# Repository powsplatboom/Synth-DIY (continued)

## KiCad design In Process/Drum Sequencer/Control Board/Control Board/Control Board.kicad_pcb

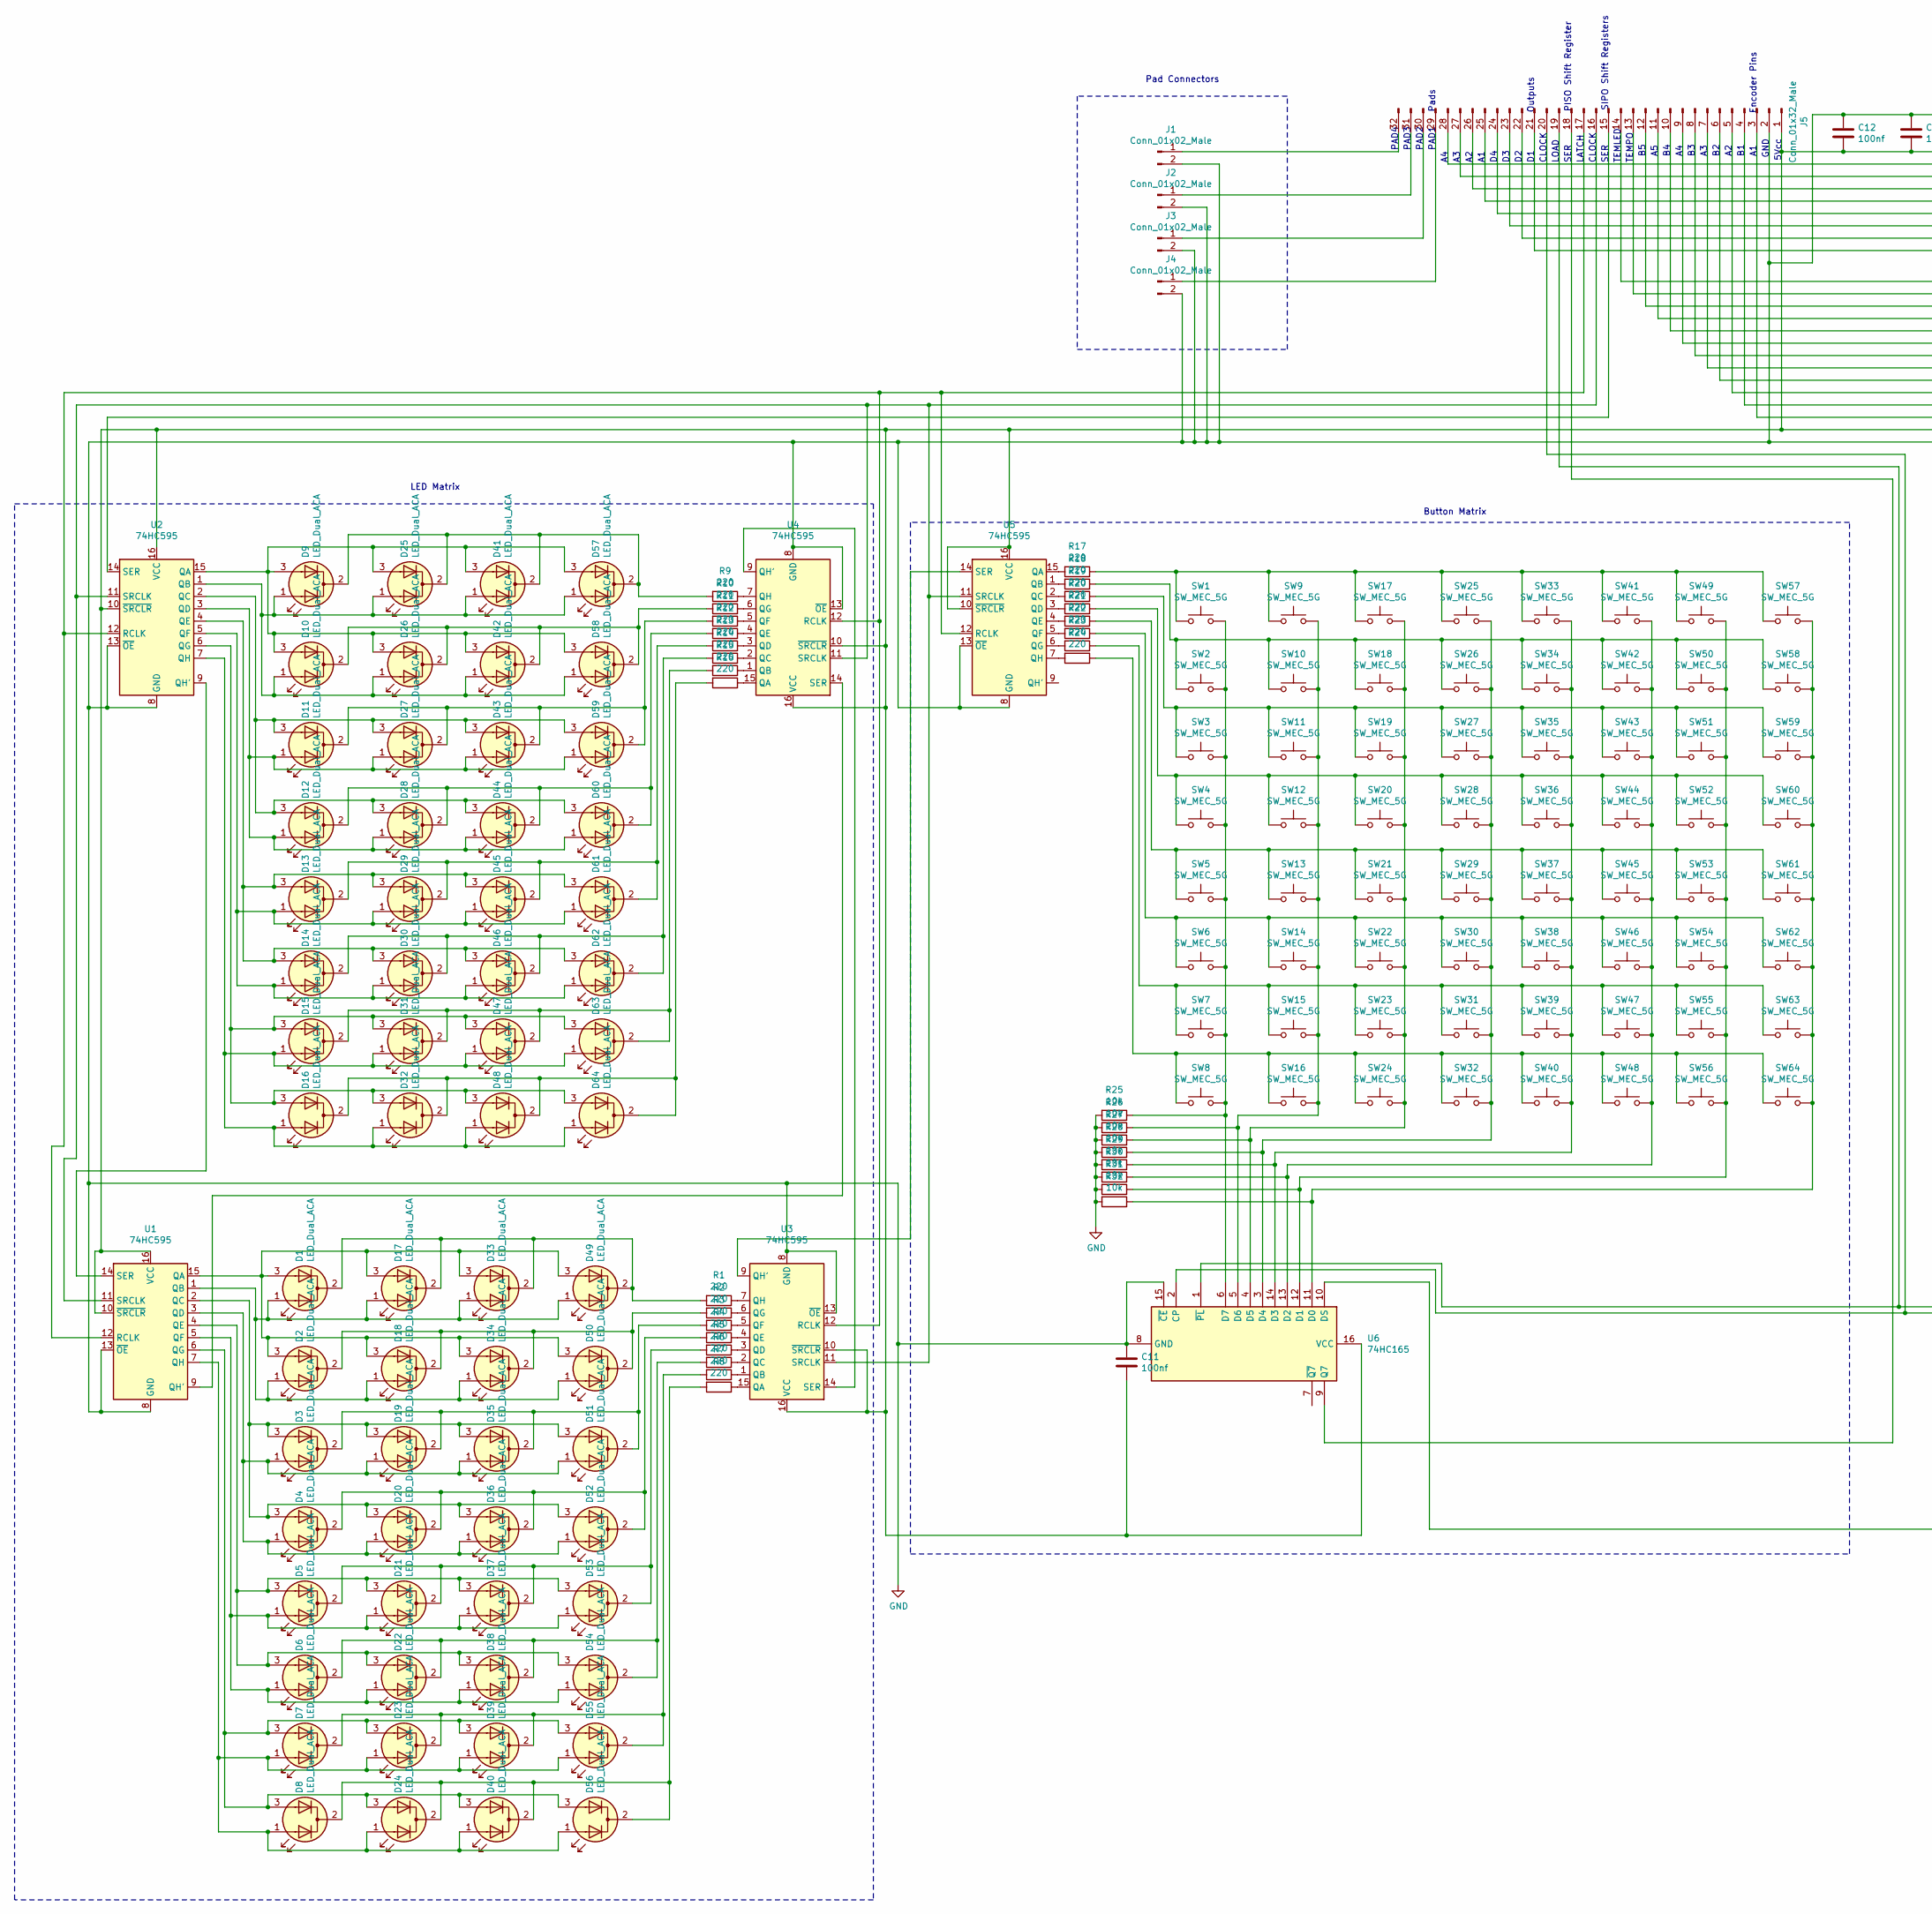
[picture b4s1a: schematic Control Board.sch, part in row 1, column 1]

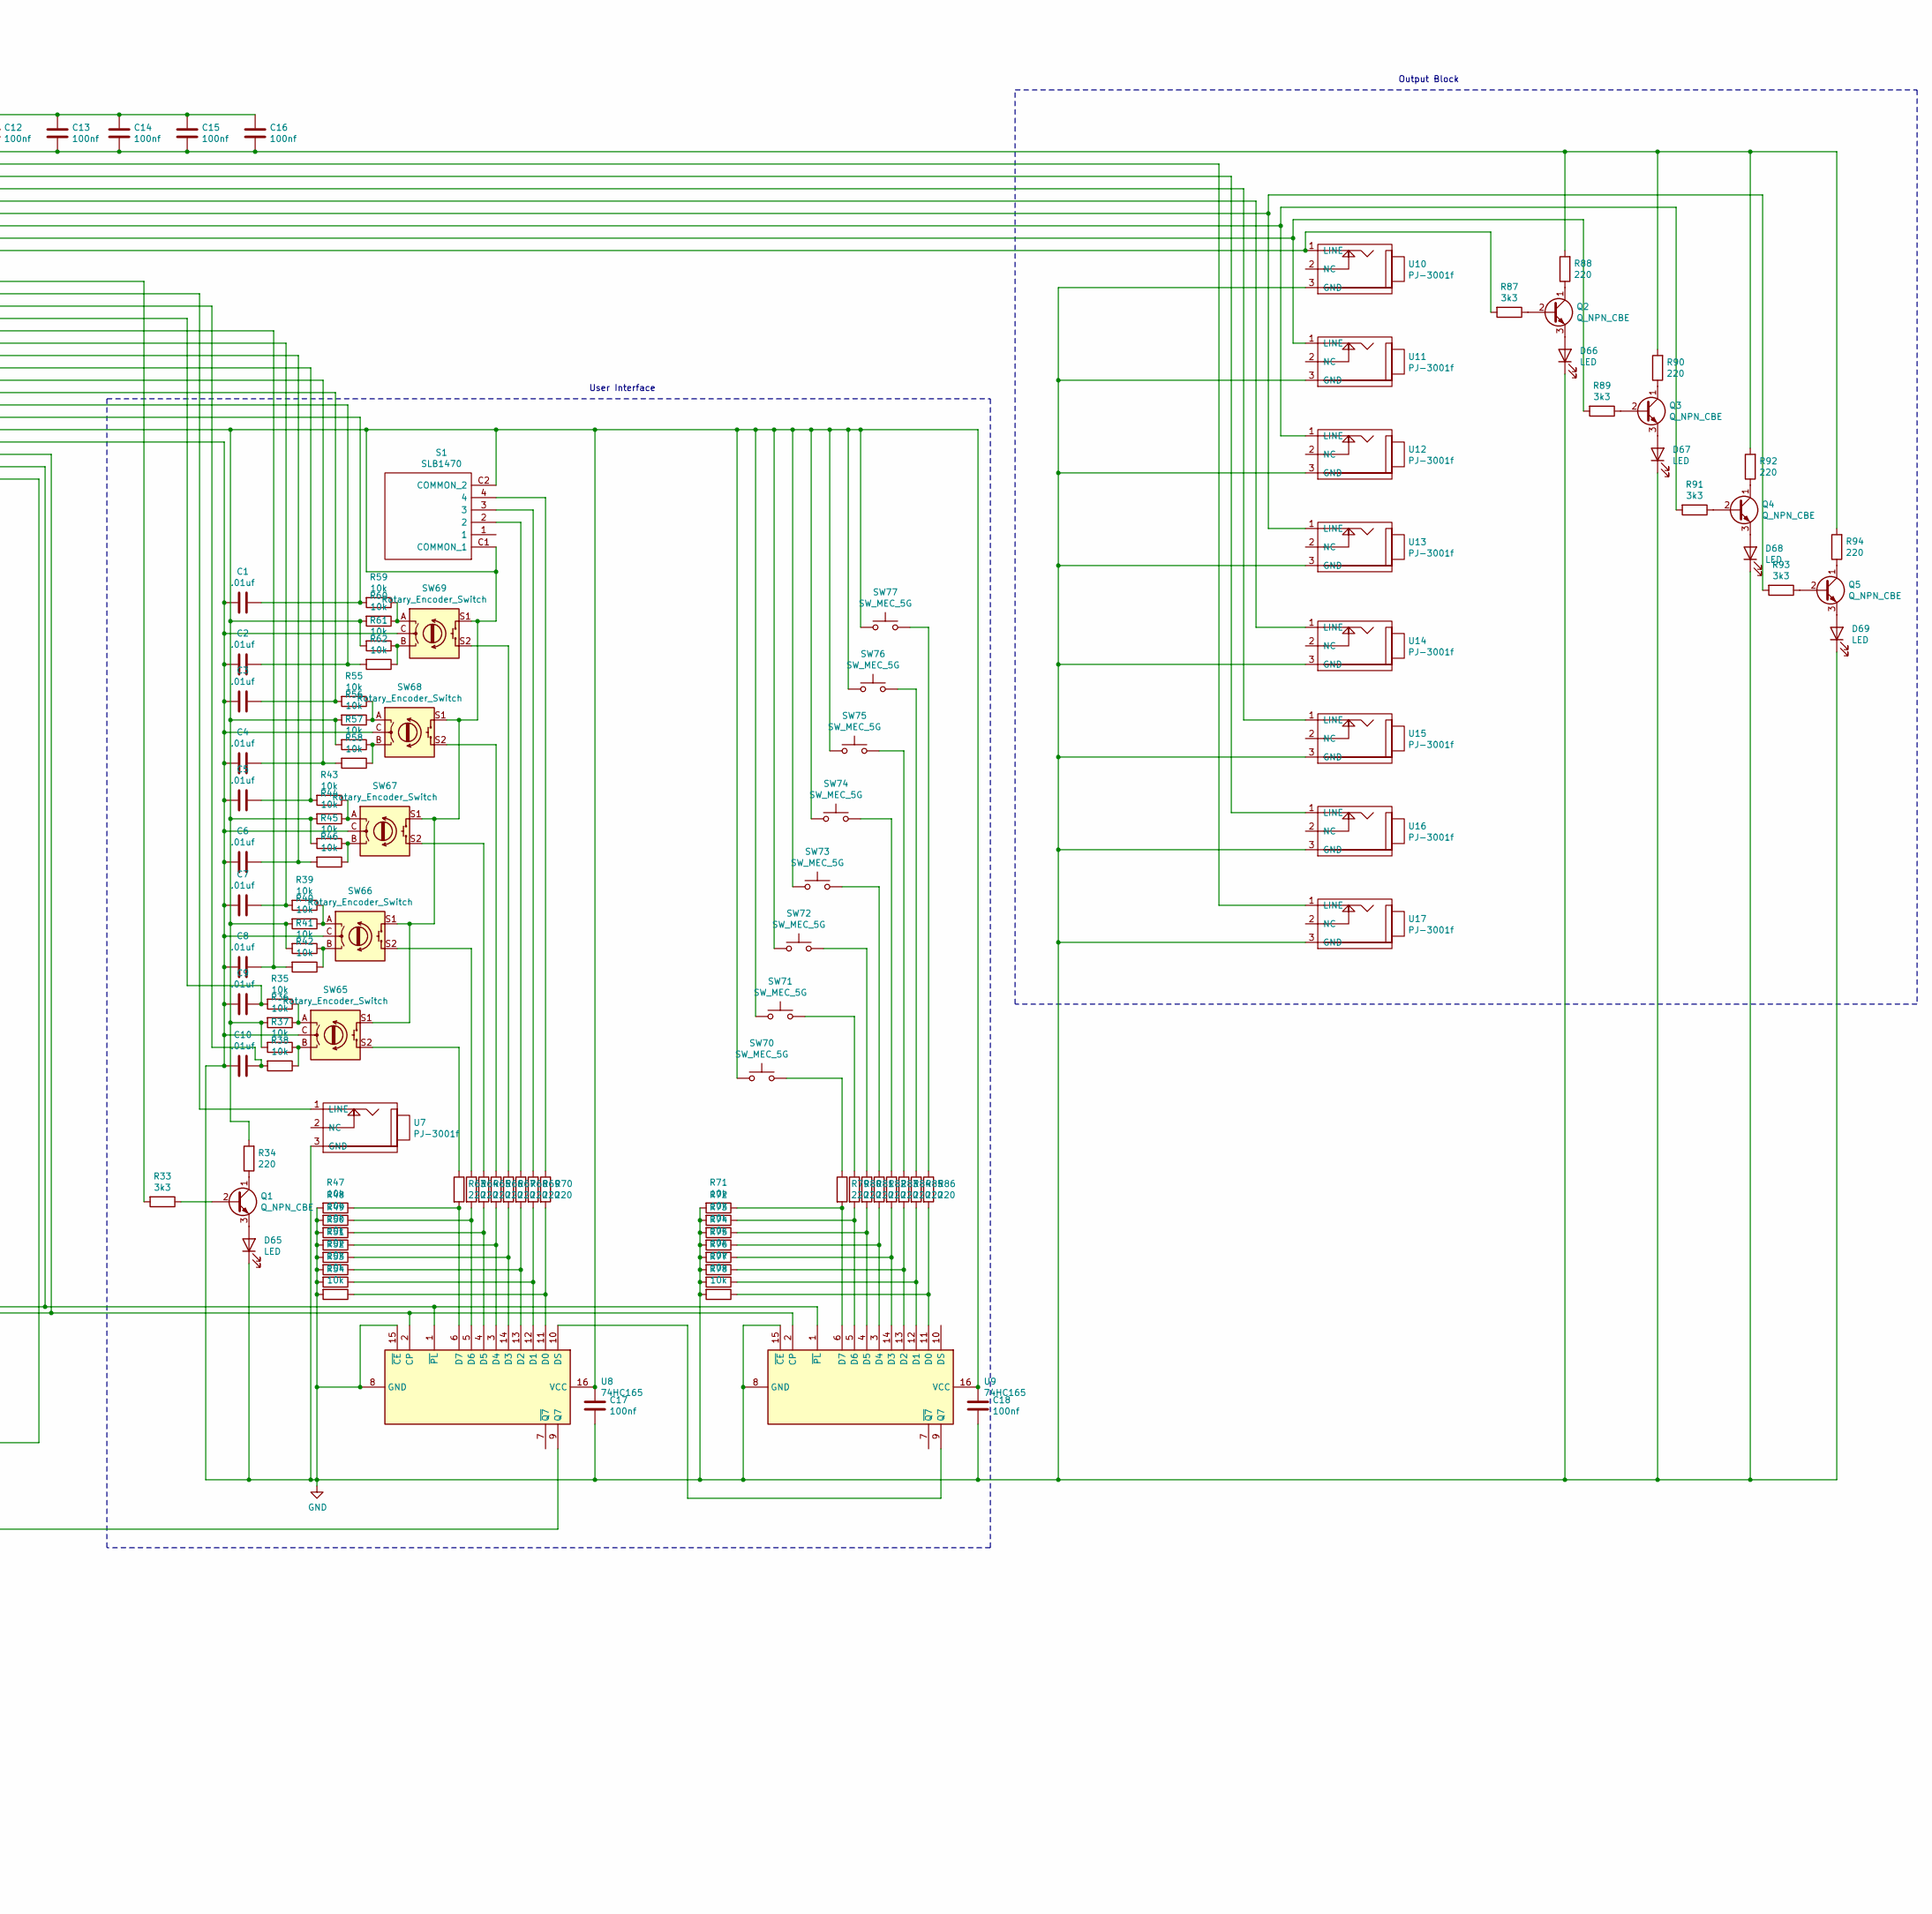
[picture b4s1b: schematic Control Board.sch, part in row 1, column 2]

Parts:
C1, C2, C3, C4, C5, C6, C7, C8, C9, C10: .01uf; C_0805_2012Metric
C11, C12, C13, C14, C15, C16, C17, C18: 100nf; C_0805_2012Metric
D1, D2, D3, D4, D5, D6, D7, D8, D9, D10, D11, D12, D13, D14, D15, D16, D17, D18, D19, D20, D21, D22, D23, D24, D25, D26, D27, D28, D29, D30, D31, D32, D33, D34, D35, D36, D37, D38, D39, D40, D41, D42, D43, D44, D45, D46, D47, D48, D49, D50, D51, D52, D53, D54, D55, D56, D57, D58, D59, D60, D61, D62, D63, D64: LED_Dual_ACA; LED_D3.0mm-3
D65, D66, D67, D68, D69: LED; LED_D5.0mm
J1, J2, J3, J4: Conn_01x02_Male; JST_XH_B2B-XH-AM_1x02_P2.50mm_Vertical
J5: Conn_01x32_Male; PinHeader_1x32_P2.54mm_Vertical
Q1, Q2, Q3, Q4, Q5: Q_NPN_CBE; TO-92_Inline
R1, R2, R3, R4, R5, R6, R7, R8, R9, R10, R11, R12, R13, R14, R15, R16, R17, R18, R19, R20, R21, R22, R23, R24, R34, R63, R64, R65, R66, R67, R68, R69, R70, R79, R80, R81, R82, R83, R84, R85, R86, R88, R90, R92, R94: 220; R_1206_3216Metric_Pad1.30x1.75mm_HandSolder
R25, R26, R27, R28, R29, R30, R31, R32, R35, R36, R37, R38, R39, R40, R41, R42, R43, R44, R45, R46, R47, R48, R49, R50, R51, R52, R53, R54, R55, R56, R57, R58, R59, R60, R61, R62, R71, R72, R73, R74, R75, R76, R77, R78: 10k; R_1206_3216Metric_Pad1.30x1.75mm_HandSolder
R33, R87, R89, R91, R93: 3k3; R_0805_2012Metric_Pad1.20x1.40mm_HandSolder
S1: SLB1470; Manufacturer_Part_Number SLB1470; Mouser Part Number 642-SLB1470
SW1, SW2, SW3, SW4, SW5, SW6, SW7, SW8, SW9, SW10, SW11, SW12, SW13, SW14, SW15, SW16, SW17, SW18, SW19, SW20, SW21, SW22, SW23, SW24, SW25, SW26, SW27, SW28, SW29, SW30, SW31, SW32, SW33, SW34, SW35, SW36, SW37, SW38, SW39, SW40, SW41, SW42, SW43, SW44, SW45, SW46, SW47, SW48, SW49, SW50, SW51, SW52, SW53, SW54, SW55, SW56, SW57, SW58, SW59, SW60, SW61, SW62, SW63, SW64, SW70, SW71, SW72, SW73, SW74, SW75, SW76, SW77: SW_MEC_5G; SW_PUSH_6mm
SW65, SW66, SW67, SW68, SW69: Rotary_Encoder_Switch; RotaryEncoder_Alps_EC11E-Switch_Vertical_H20mm
U1, U2, U3, U4, U5: 74HC595; SO-16_3.9x9.9mm_P1.27mm
U6, U8: 74HC165; SO-16_3.9x9.9mm_P1.27mm
U7, U10, U11, U12, U13, U14, U15, U16, U17: PJ-3001f; PJ-3001_Mono_Phone
U9: 74HC165; SOIC-16_3.9x9.9mm_P1.27mm

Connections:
GND: C1.2, C2.2, C3.2, C4.2, C5.2, C6.2, C7.2, C8.2, C9.2, C10.2, C11.1, C12.1, C13.1, C14.1, C15.1, C16.1, C17.2, C18.2, D65.1 (K), D66.1 (K), D67.1 (K), D68.1 (K), D69.1 (K), J1.2, J2.2, J3.2, J4.2, J5.2, R25.2, R26.2, R27.2, R28.2, R29.2, R30.2, R31.2, R32.2, R47.2, R48.2, R49.2, R50.2, R51.2, R52.2, R53.2, R54.2, R71.2, R72.2, R73.2, R74.2, R75.2, R76.2, R77.2, R78.2, SW65.C, SW66.C, SW67.C, SW68.C, SW69.C, U1.8 (GND), U1.13 (~OE), U2.8 (GND), U2.13 (~OE), U3.8 (GND), U3.13 (~OE), U4.8 (GND), U4.13 (~OE), U5.8 (GND), U5.13 (~OE), U6.8 (GND), U6.15 (~CE), U7.3 (GND), U8.8 (GND), U8.15 (~CE), U9.8 (GND), U9.15 (~CE), U10.3 (GND), U11.3 (GND), U12.3 (GND), U13.3 (GND), U14.3 (GND), U15.3 (GND), U16.3 (GND), U17.3 (GND)
unnamed: C1.1, J5.3, R59.2
unnamed: C2.1, J5.4, R62.2
unnamed: C3.1, J5.5, R55.2
unnamed: C4.1, J5.6, R58.2
unnamed: C5.1, J5.7, R43.2
unnamed: C6.1, J5.8, R46.2
unnamed: C7.1, J5.9, R39.2
unnamed: C8.1, J5.10, R42.2
unnamed: C9.1, J5.11, R35.2
unnamed: C10.1, J5.12, R38.2
unnamed: C11.2, C12.2, C13.2, C14.2, C15.2, C16.2, C17.1, C18.1, J5.1, R34.2, R36.2, R37.2, R40.2, R41.2, R44.2, R45.2, R56.2, R57.2, R60.2, R61.2, R88.2, R90.2, R92.2, R94.2, S1.C1 (COMMON_1), S1.C2 (COMMON_2), SW65.S1, SW66.S1, SW67.S1, SW68.S1, SW69.S1, SW70.1 (A), SW71.1 (A), SW72.1 (A), SW73.1 (A), SW74.1 (A), SW75.1 (A), SW76.1 (A), SW77.1 (A), U1.10 (~SRCLR), U1.16 (VCC), U2.10 (~SRCLR), U2.16 (VCC), U3.10 (~SRCLR), U3.16 (VCC), U4.10 (~SRCLR), U4.16 (VCC), U5.10 (~SRCLR), U5.16 (VCC), U6.16 (VCC), U8.16 (VCC), U9.16 (VCC)
unnamed: D1.1 (A1), D2.1 (A1), D17.1 (A1), D18.1 (A1), D33.1 (A1), D34.1 (A1), D49.1 (A1), D50.1 (A1), U1.1 (QB)
unnamed: D1.2 (K), D17.2 (K), D33.2 (K), D49.2 (K), R1.2
unnamed: D1.3 (A2), D2.3 (A2), D17.3 (A2), D18.3 (A2), D33.3 (A2), D34.3 (A2), D49.3 (A2), D50.3 (A2), U1.15 (QA)
unnamed: D9.1 (A1), D10.1 (A1), D25.1 (A1), D26.1 (A1), D41.1 (A1), D42.1 (A1), D57.1 (A1), D58.1 (A1), U2.1 (QB)
unnamed: D10.2 (K), D26.2 (K), D42.2 (K), D58.2 (K), R10.2
unnamed: D9.3 (A2), D10.3 (A2), D25.3 (A2), D26.3 (A2), D41.3 (A2), D42.3 (A2), D57.3 (A2), D58.3 (A2), U2.15 (QA)
unnamed: D11.1 (A1), D12.1 (A1), D27.1 (A1), D28.1 (A1), D43.1 (A1), D44.1 (A1), D59.1 (A1), D60.1 (A1), U2.3 (QD)
unnamed: D11.2 (K), D27.2 (K), D43.2 (K), D59.2 (K), R11.2
unnamed: D11.3 (A2), D12.3 (A2), D27.3 (A2), D28.3 (A2), D43.3 (A2), D44.3 (A2), D59.3 (A2), D60.3 (A2), U2.2 (QC)
unnamed: D12.2 (K), D28.2 (K), D44.2 (K), D60.2 (K), R12.2
unnamed: D13.1 (A1), D14.1 (A1), D29.1 (A1), D30.1 (A1), D45.1 (A1), D46.1 (A1), D61.1 (A1), D62.1 (A1), U2.5 (QF)
unnamed: D13.2 (K), D29.2 (K), D45.2 (K), D61.2 (K), R13.2
unnamed: D13.3 (A2), D14.3 (A2), D29.3 (A2), D30.3 (A2), D45.3 (A2), D46.3 (A2), D61.3 (A2), D62.3 (A2), U2.4 (QE)
unnamed: D14.2 (K), D30.2 (K), D46.2 (K), D62.2 (K), R14.2
unnamed: D15.1 (A1), D16.1 (A1), D31.1 (A1), D32.1 (A1), D47.1 (A1), D48.1 (A1), D63.1 (A1), D64.1 (A1), U2.7 (QH)
unnamed: D15.2 (K), D31.2 (K), D47.2 (K), D63.2 (K), R15.2
unnamed: D15.3 (A2), D16.3 (A2), D31.3 (A2), D32.3 (A2), D47.3 (A2), D48.3 (A2), D63.3 (A2), D64.3 (A2), U2.6 (QG)
unnamed: D16.2 (K), D32.2 (K), D48.2 (K), D64.2 (K), R16.2
unnamed: D2.2 (K), D18.2 (K), D34.2 (K), D50.2 (K), R2.2
unnamed: D3.1 (A1), D4.1 (A1), D19.1 (A1), D20.1 (A1), D35.1 (A1), D36.1 (A1), D51.1 (A1), D52.1 (A1), U1.3 (QD)
unnamed: D3.2 (K), D19.2 (K), D35.2 (K), D51.2 (K), R3.2
unnamed: D3.3 (A2), D4.3 (A2), D19.3 (A2), D20.3 (A2), D35.3 (A2), D36.3 (A2), D51.3 (A2), D52.3 (A2), U1.2 (QC)
unnamed: D4.2 (K), D20.2 (K), D36.2 (K), D52.2 (K), R4.2
unnamed: D5.1 (A1), D6.1 (A1), D21.1 (A1), D22.1 (A1), D37.1 (A1), D38.1 (A1), D53.1 (A1), D54.1 (A1), U1.5 (QF)
unnamed: D5.2 (K), D21.2 (K), D37.2 (K), D53.2 (K), R5.2
unnamed: D5.3 (A2), D6.3 (A2), D21.3 (A2), D22.3 (A2), D37.3 (A2), D38.3 (A2), D53.3 (A2), D54.3 (A2), U1.4 (QE)
unnamed: D6.2 (K), D22.2 (K), D38.2 (K), D54.2 (K), R6.2
unnamed: D7.1 (A1), D8.1 (A1), D23.1 (A1), D24.1 (A1), D39.1 (A1), D40.1 (A1), D55.1 (A1), D56.1 (A1), U1.7 (QH)
unnamed: D7.2 (K), D23.2 (K), D39.2 (K), D55.2 (K), R7.2
unnamed: D7.3 (A2), D8.3 (A2), D23.3 (A2), D24.3 (A2), D39.3 (A2), D40.3 (A2), D55.3 (A2), D56.3 (A2), U1.6 (QG)
unnamed: D8.2 (K), D24.2 (K), D40.2 (K), D56.2 (K), R8.2
unnamed: D9.2 (K), D25.2 (K), D41.2 (K), D57.2 (K), R9.2
unnamed: D65.2 (A), Q1.3 (E)
unnamed: D66.2 (A), Q2.3 (E)
unnamed: D67.2 (A), Q3.3 (E)
unnamed: D68.2 (A), Q4.3 (E)
unnamed: D69.2 (A), Q5.3 (E)
unnamed: J1.1, J5.32
unnamed: J2.1, J5.31
unnamed: J3.1, J5.30
unnamed: J4.1, J5.29
unnamed: J5.13, U7.1 (LINE)
unnamed: J5.14, R33.2
unnamed: J5.15, U2.14 (SER)
unnamed: J5.16, U1.11 (SRCLK), U2.11 (SRCLK), U3.11 (SRCLK), U4.11 (SRCLK), U5.11 (SRCLK)
unnamed: J5.17, U1.12 (RCLK), U2.12 (RCLK), U3.12 (RCLK), U4.12 (RCLK), U5.12 (RCLK)
unnamed: J5.18, U6.9 (Q7)
unnamed: J5.19, U6.1 (~PL), U8.1 (~PL), U9.1 (~PL)
unnamed: J5.20, U6.2 (CP), U8.2 (CP), U9.2 (CP)
unnamed: J5.21, R87.2, U10.1 (LINE)
unnamed: J5.22, R89.2, U11.1 (LINE)
unnamed: J5.23, R91.2, U12.1 (LINE)
unnamed: J5.24, R93.2, U13.1 (LINE)
unnamed: J5.25, U14.1 (LINE)
unnamed: J5.26, U15.1 (LINE)
unnamed: J5.27, U16.1 (LINE)
unnamed: J5.28, U17.1 (LINE)
unnamed: Q1.1 (C), R34.1
unnamed: Q1.2 (B), R33.1
unnamed: Q2.1 (C), R88.1
unnamed: Q2.2 (B), R87.1
unnamed: Q3.1 (C), R90.1
unnamed: Q3.2 (B), R89.1
unnamed: Q4.1 (C), R92.1
unnamed: Q4.2 (B), R91.1
unnamed: Q5.1 (C), R94.1
unnamed: Q5.2 (B), R93.1
unnamed: R1.1, U3.7 (QH)
unnamed: R2.1, U3.6 (QG)
unnamed: R3.1, U3.5 (QF)
unnamed: R4.1, U3.4 (QE)
unnamed: R5.1, U3.3 (QD)
unnamed: R6.1, U3.2 (QC)
unnamed: R7.1, U3.1 (QB)
unnamed: R8.1, U3.15 (QA)
unnamed: R9.1, U4.7 (QH)
unnamed: R10.1, U4.6 (QG)
unnamed: R11.1, U4.5 (QF)
unnamed: R12.1, U4.4 (QE)
unnamed: R13.1, U4.3 (QD)
unnamed: R14.1, U4.2 (QC)
unnamed: R15.1, U4.1 (QB)
unnamed: R16.1, U4.15 (QA)
unnamed: R17.1, SW1.1 (A), SW9.1 (A), SW17.1 (A), SW25.1 (A), SW33.1 (A), SW41.1 (A), SW49.1 (A), SW57.1 (A)
unnamed: R17.2, U5.15 (QA)
unnamed: R18.1, SW2.1 (A), SW10.1 (A), SW18.1 (A), SW26.1 (A), SW34.1 (A), SW42.1 (A), SW50.1 (A), SW58.1 (A)
unnamed: R18.2, U5.1 (QB)
unnamed: R19.1, SW3.1 (A), SW11.1 (A), SW19.1 (A), SW27.1 (A), SW35.1 (A), SW43.1 (A), SW51.1 (A), SW59.1 (A)
unnamed: R19.2, U5.2 (QC)
unnamed: R20.1, SW4.1 (A), SW12.1 (A), SW20.1 (A), SW28.1 (A), SW36.1 (A), SW44.1 (A), SW52.1 (A), SW60.1 (A)
unnamed: R20.2, U5.3 (QD)
unnamed: R21.1, SW5.1 (A), SW13.1 (A), SW21.1 (A), SW29.1 (A), SW37.1 (A), SW45.1 (A), SW53.1 (A), SW61.1 (A)
unnamed: R21.2, U5.4 (QE)
unnamed: R22.1, SW6.1 (A), SW14.1 (A), SW22.1 (A), SW30.1 (A), SW38.1 (A), SW46.1 (A), SW54.1 (A), SW62.1 (A)
unnamed: R22.2, U5.5 (QF)
unnamed: R23.1, SW7.1 (A), SW15.1 (A), SW23.1 (A), SW31.1 (A), SW39.1 (A), SW47.1 (A), SW55.1 (A), SW63.1 (A)
unnamed: R23.2, U5.6 (QG)
unnamed: R24.1, SW8.1 (A), SW16.1 (A), SW24.1 (A), SW32.1 (A), SW40.1 (A), SW48.1 (A), SW56.1 (A), SW64.1 (A)
unnamed: R24.2, U5.7 (QH)
unnamed: R25.1, SW1.2 (B), SW2.2 (B), SW3.2 (B), SW4.2 (B), SW5.2 (B), SW6.2 (B), SW7.2 (B), SW8.2 (B), U6.6 (D7)
unnamed: R26.1, SW9.2 (B), SW10.2 (B), SW11.2 (B), SW12.2 (B), SW13.2 (B), SW14.2 (B), SW15.2 (B), SW16.2 (B), U6.5 (D6)
unnamed: R27.1, SW17.2 (B), SW18.2 (B), SW19.2 (B), SW20.2 (B), SW21.2 (B), SW22.2 (B), SW23.2 (B), SW24.2 (B), U6.4 (D5)
unnamed: R28.1, SW25.2 (B), SW26.2 (B), SW27.2 (B), SW28.2 (B), SW29.2 (B), SW30.2 (B), SW31.2 (B), SW32.2 (B), U6.3 (D4)
unnamed: R29.1, SW33.2 (B), SW34.2 (B), SW35.2 (B), SW36.2 (B), SW37.2 (B), SW38.2 (B), SW39.2 (B), SW40.2 (B), U6.14 (D3)
unnamed: R30.1, SW41.2 (B), SW42.2 (B), SW43.2 (B), SW44.2 (B), SW45.2 (B), SW46.2 (B), SW47.2 (B), SW48.2 (B), U6.13 (D2)
unnamed: R31.1, SW49.2 (B), SW50.2 (B), SW51.2 (B), SW52.2 (B), SW53.2 (B), SW54.2 (B), SW55.2 (B), SW56.2 (B), U6.12 (D1)
unnamed: R32.1, SW57.2 (B), SW58.2 (B), SW59.2 (B), SW60.2 (B), SW61.2 (B), SW62.2 (B), SW63.2 (B), SW64.2 (B), U6.11 (D0)
unnamed: R35.1, R36.1, SW65.A
unnamed: R37.1, R38.1, SW65.B
unnamed: R39.1, R40.1, SW66.A
unnamed: R41.1, R42.1, SW66.B
unnamed: R43.1, R44.1, SW67.A
unnamed: R45.1, R46.1, SW67.B
unnamed: R47.1, R63.2, U8.6 (D7)
unnamed: R48.1, R64.2, U8.5 (D6)
unnamed: R49.1, R65.2, U8.4 (D5)
unnamed: R50.1, R66.2, U8.3 (D4)
unnamed: R51.1, R67.2, U8.14 (D3)
unnamed: R52.1, R68.2, U8.13 (D2)
unnamed: R53.1, R69.2, U8.12 (D1)
unnamed: R54.1, R70.2, U8.11 (D0)
unnamed: R55.1, R56.1, SW68.A
unnamed: R57.1, R58.1, SW68.B
unnamed: R59.1, R60.1, SW69.A
unnamed: R61.1, R62.1, SW69.B
unnamed: R63.1, SW65.S2
unnamed: R64.1, SW66.S2
unnamed: R65.1, SW67.S2
unnamed: R66.1, SW68.S2
unnamed: R67.1, SW69.S2
unnamed: R68.1, S1.2
unnamed: R69.1, S1.3
unnamed: R70.1, S1.4
unnamed: R71.1, R79.2, U9.6 (D7)
unnamed: R72.1, R80.2, U9.5 (D6)
unnamed: R73.1, R81.2, U9.4 (D5)
unnamed: R74.1, R82.2, U9.3 (D4)
unnamed: R75.1, R83.2, U9.14 (D3)
unnamed: R76.1, R84.2, U9.13 (D2)
unnamed: R77.1, R85.2, U9.12 (D1)
unnamed: R78.1, R86.2, U9.11 (D0)
unnamed: R79.1, SW70.2 (B)
unnamed: R80.1, SW71.2 (B)
unnamed: R81.1, SW72.2 (B)
unnamed: R82.1, SW73.2 (B)
unnamed: R83.1, SW74.2 (B)
unnamed: R84.1, SW75.2 (B)
unnamed: R85.1, SW76.2 (B)
unnamed: R86.1, SW77.2 (B)
unnamed: U1.9 (QH'), U4.14 (SER)
unnamed: U1.14 (SER), U2.9 (QH')
unnamed: U3.9 (QH'), U5.14 (SER)
unnamed: U3.14 (SER), U4.9 (QH')
unnamed: U6.10 (DS), U8.9 (Q7)
unnamed: U8.10 (DS), U9.9 (Q7)

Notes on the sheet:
5Vcc
GND
Encoder Pins
SIPO Shift Registers
PISO Shift Register
Outputs
Pads
SER
CLOCK
LATCH
LOAD
LED Matrix
Button Matrix
User Interface
Output Block
TEMPO
TEMLED
PAD1
PAD2
PAD3
PAD4
Pad Connectors

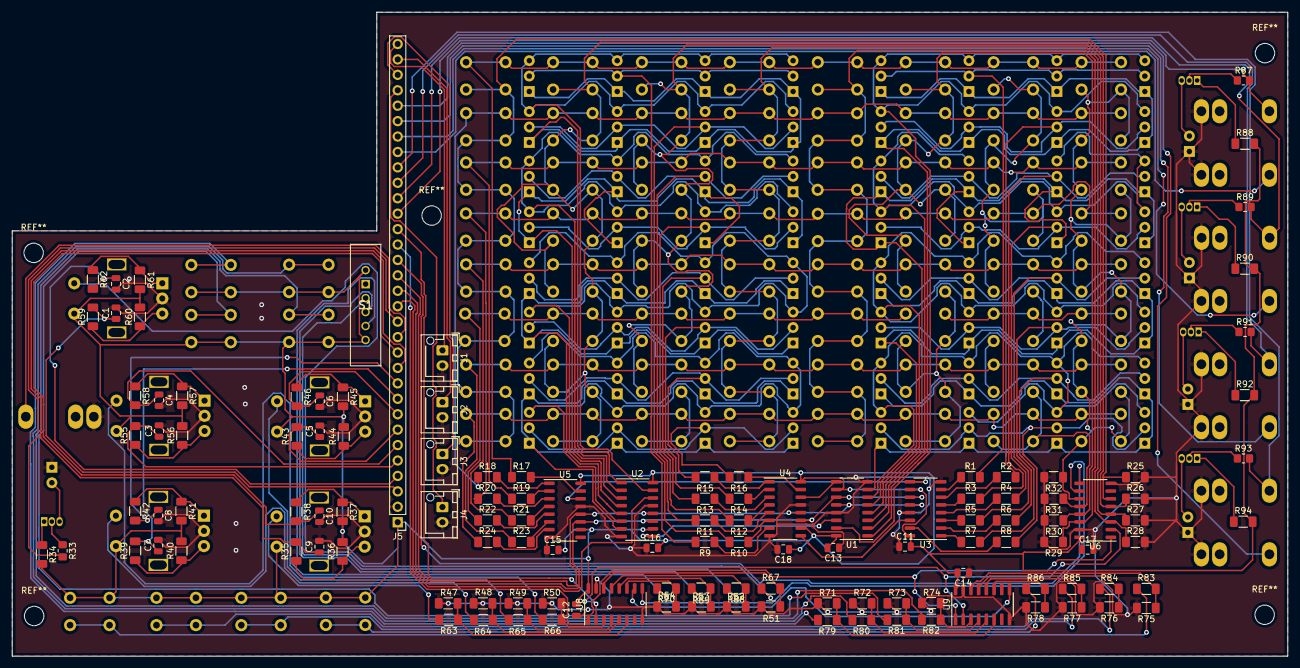
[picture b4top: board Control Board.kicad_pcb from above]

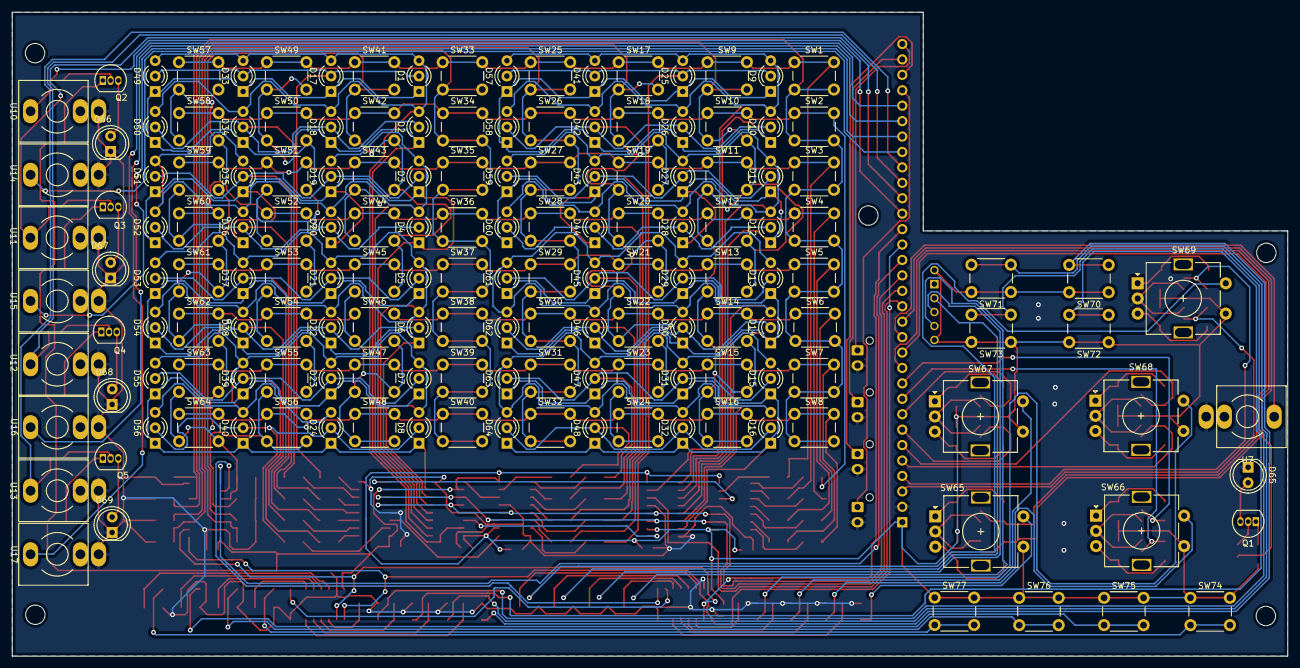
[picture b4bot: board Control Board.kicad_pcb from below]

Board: 2 copper layers, 210.0 x 106.0 mm, 286 parts (160 on the bottom side), 167 nets.

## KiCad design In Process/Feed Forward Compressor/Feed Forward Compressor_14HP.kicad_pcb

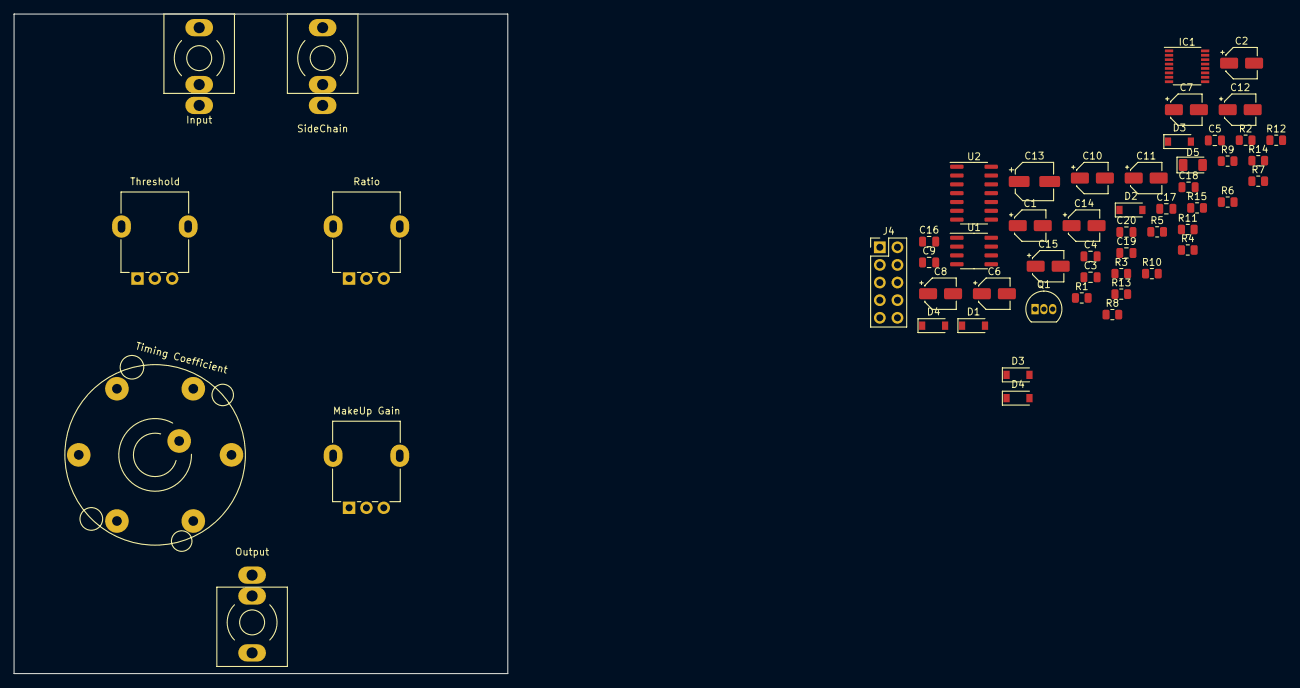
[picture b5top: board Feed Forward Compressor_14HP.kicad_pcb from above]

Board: 2 copper layers, 71.1 x 95.0 mm, 54 parts (0 on the bottom side), 36 nets, no tracks yet.

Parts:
C1, C2, C11, C14, C15: 10u; CP_Elec_4x5.3
C3: 100p; C_0805_2012Metric
C4, C5, C18, C19, C20: 100n; C_0805_2012Metric
C6, C12: 22u; CP_Elec_4x5.3
C7: 1u; CP_Elec_4x5.3
C8: 3u3; CP_Elec_4x5.3
C9, C16: 22p; C_0805_2012Metric
C10: 6u8; CP_Elec_4x5.4
C13: 33u; CP_Elec_5x5.3
C17: 0.33u; C_0805_2012Metric
D1, D2: B5819W; D_SOD-123
D3, D4: 1N4148; D_SOD-123
D3#2, D4#2: 1n4148; D_SOD-123
D5: LED; LED_1206_3216Metric
IC1: THAT4305Q16-U; SSOP-16_3.9x4.9mm_P0.635mm
Input: PJ301_THONKICONN1; PJ-3001_Mono_Phone
J4: Conn_02x05_Odd_Even; PinHeader_2x05_P2.54mm_Vertical
MakeUp Gain: 10k; Potentiometer_Alpha_RD901F-40-00D_Single_Vertical
Output: PJ301_THONKICONN1; PJ-3001_Mono_Phone
Q1: 2N3904; TO-92_Inline
R1, R4: 20k; R_0805_2012Metric
R2: 33k; R_0805_2012Metric
R3: 6k2; R_0805_2012Metric
R5, R13: 5k1; R_0805_2012Metric
R6: 360k; R_0805_2012Metric
R7, R10, R14: 10k; R_0805_2012Metric
R8: 1k43; R_0805_2012Metric
R9: 487k; R_0805_2012Metric
R11: 100k; R_0805_2012Metric
R12: 5k; R_0805_2012Metric
R15: 1k; R_0805_2012Metric
Ratio: 10k; Potentiometer_Alpha_RD901F-40-00D_Single_Vertical
SideChain: PJ301_THONKICONN1; PJ-3001_Mono_Phone
Threshold: 10k; Potentiometer_Alpha_RD901F-40-00D_Single_Vertical
Timing Coefficient: SR2616F-0106-18F5B-D8-N; SR2616F-0106
U1: L78L05_SO8; SOIC-8_3.9x4.9mm_P1.27mm
U2: TL074; SOIC-14_3.9x8.7mm_P1.27mm

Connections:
+5V: C18.1, U1.1
+12V: C4.1, C6.1, C14.1, C17.1, C19.2, D1.1, IC1.9, MakeUp Gain.1, R15.2, Threshold.1, U1.8, U2.4
-12V: C5.1, C15.2, C20.2, D2.2, IC1.8, MakeUp Gain.3, Q1.1, Threshold.3, U2.11
GND: C3.1, C4.2, C5.2, C6.2, C7.2, C8.2, C10.2, C11.2, C12.2, C13.2, C14.2, C15.1, C17.2, C18.2, C19.1, C20.1, IC1.11, Input.1, J4.3, J4.4, J4.5, J4.6, J4.7, J4.8, Output.1, R12.1, Ratio.1, SideChain.1, U1.2, U1.3, U1.6, U1.7, U2.3, U2.5, U2.10
LED_drive: R8.1, R10.2, Ratio.2, U2.12
unnamed: C1.1, R1.2
unnamed: C1.2, Input.3, Output.2
unnamed: C2.1, R2.2
unnamed: C2.2, Output.3
unnamed: C3.2, R3.2
unnamed: C7.1, Timing Coefficient.1
unnamed: C8.1, Timing Coefficient.3
unnamed: C9.1, IC1.13, R4.2, U2.2
unnamed: C9.2, R4.1, SideChain.3, U2.1
unnamed: C10.1, Timing Coefficient.5
unnamed: C11.1, Timing Coefficient.7
unnamed: C12.1, Timing Coefficient.9
unnamed: C13.1, Timing Coefficient.11
unnamed: C16.1, D3#2.1, R5.1, R6.1, R7.2, U2.6
unnamed: C16.2, D3#2.2, D4#2.1, U2.7
unnamed: D1.2, J4.9, J4.10
unnamed: D2.1, J4.1, J4.2
unnamed: D5.1, Q1.3
unnamed: D5.2, R15.1
unnamed: IC1.2, R2.1
unnamed: IC1.4, Timing Coefficient.A1
unnamed: IC1.15, R1.1, R3.1
unnamed: Q1.2, R14.2
unnamed: R6.2, Threshold.2
unnamed: MakeUp Gain.2, R9.2
unnamed: R9.1, R10.1, R13.2, U2.9
unnamed: R11.1, R12.2, U2.13
unnamed: R11.2, R14.1, U2.14
RMS_out: IC1.5, R5.2
Threshold_out: D4#2.2, R7.1, R8.2, Ratio.3
V_Comp: IC1.12, R13.1, U2.8
